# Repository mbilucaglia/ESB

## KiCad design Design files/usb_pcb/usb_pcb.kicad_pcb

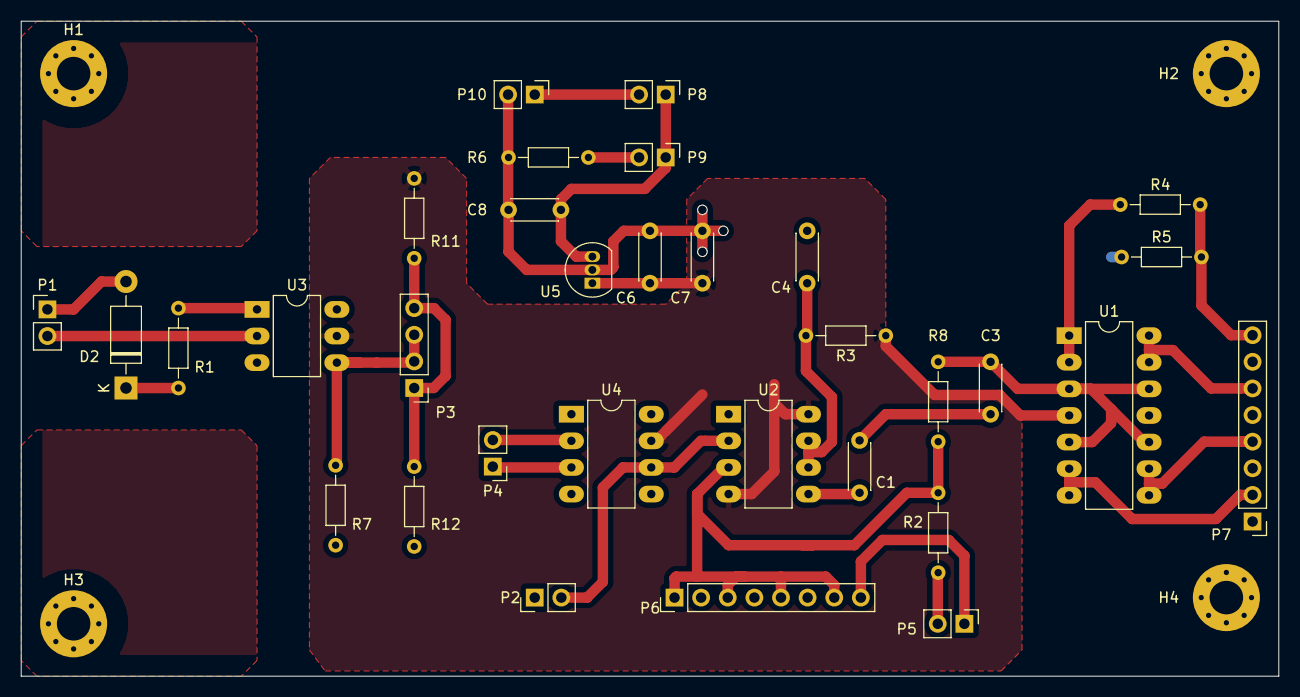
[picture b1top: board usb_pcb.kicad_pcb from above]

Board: 2 copper layers, 120.0 x 62.5 mm, 36 parts (0 on the bottom side), 24 nets.

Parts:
C1: 10n; C_Disc_D4.3mm_W1.9mm_P5.00mm
C3: 1n; C_Disc_D4.3mm_W1.9mm_P5.00mm
C4, C7: 100n; C_Disc_D4.3mm_W1.9mm_P5.00mm
C6: 1u; C_Disc_D4.3mm_W1.9mm_P5.00mm
C8: 1u,35V; C_Disc_D4.3mm_W1.9mm_P5.00mm
D2: 1N4007; D_DO-41_SOD81_P10.16mm_Horizontal
H1, H3: MountingHole; MountingHole_3.2mm_M3_Pad_Via
H2, H4: MountingHole_Pad; MountingHole_3.2mm_M3_Pad_Via
P1, P2, P4, P5, P8, P9, P10: Conn_01x02_Male; PinHeader_1x02_P2.54mm_Vertical
P3: Conn_01x05_Male; PinHeader_1x04_P2.54mm_Vertical
P6, P7: Conn_01x08_Male; PinHeader_1x08_P2.54mm_Vertical
R1: 680R; R_Axial_DIN0204_L3.6mm_D1.6mm_P7.62mm_Horizontal
R2: 270R; R_Axial_DIN0204_L3.6mm_D1.6mm_P7.62mm_Horizontal
R3, R11, R12: 33k; R_Axial_DIN0204_L3.6mm_D1.6mm_P7.62mm_Horizontal
R4, R8: 100k; R_Axial_DIN0204_L3.6mm_D1.6mm_P7.62mm_Horizontal
R5: 100R; R_Axial_DIN0204_L3.6mm_D1.6mm_P7.62mm_Horizontal
R6: 220R; R_Axial_DIN0204_L3.6mm_D1.6mm_P7.62mm_Horizontal
R7: 18K; R_Axial_DIN0204_L3.6mm_D1.6mm_P7.62mm_Horizontal
U1: MCP6024-I/P; DIP-14_W7.62mm_LongPads
U2: NE555; DIP-8_W7.62mm_LongPads
U3: 4N35; DIP-6_W7.62mm_LongPads
U4: MCP6021-I/P; DIP-8_W7.62mm_LongPads
U5: L78L05_TO92; TO-92_Inline

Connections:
+5V: C6.1, C7.1, R3.1, R11.1, U1.4, U2.4, U2.8, U3.5, U4.7, U5.1
/OUT_PULSE: P6.1, P6.3, P6.5, P6.7, R2.1, R8.2, U2.3
GND: C1.2, C3.2, C4.2, C6.2, C7.2, C8.2, H2.1, H4.1, P2.1, P5.1, P6.2, P6.4, P6.6, P6.8, P7.1, P7.3, P7.5, P7.7, P10.2, R5.1, R6.1, R7.1, R12.2, U1.11, U2.1, U4.4, U5.2
unnamed: C1.1, U2.5
unnamed: C3.1, R8.1, U1.3, U1.5, U1.10, U1.12
unnamed: C4.1, R3.2, U2.6, U2.7
unnamed: C8.1, P8.1, P9.1, U5.3
unnamed: D2.1, R1.1
unnamed: D2.2, P1.1
unnamed: P1.2, U3.2
unnamed: P2.2, U2.2, U4.6
unnamed: P3.1, P3.4, R11.2, R12.1
unnamed: P3.2, P3.3, R7.2, U3.4
unnamed: P4.1, U4.3
unnamed: P4.2, U4.2
unnamed: P5.2, R2.2
unnamed: P7.2, U1.6, U1.7
unnamed: P7.4, U1.8, U1.9
unnamed: P7.6, U1.13, U1.14
unnamed: P7.8, R4.1, R5.2
unnamed: P9.2, R6.2
unnamed: P8.2, P10.1
unnamed: R1.2, U3.1
unnamed: R4.2, U1.1, U1.2

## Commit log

2020-06-10 - Cleaned up schematic file - Added pcb footprints to all components
2020-06-16 Created pcb layout and output files
2021-05-01 Ground and power planes modified. Manual trigger position modified to work with any polarity setting
2021-05-02 Minor modifications for first production run, gerber updated
